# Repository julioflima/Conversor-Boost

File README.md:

# CONVERSOR BOOST

##### UNIVERSIDADE FEDERAL DO CEARÁ, CAMPUS SOBRAL
##### 
##### ENGENHARIA ELÉTRICA, DISCIPLINA ELETRÔNICA DE POTÊNCIA
##### 

##### 1. FLÁVIA PEROZA RUIZ
##### 2. JULIO CESAR FERREIRA LIMA
##### 3. MATHEUS PIRES DE FARIAS
##### 4. YARA MACHADO OLIVEIRA

> ISSO É APENAS UM RESUMO, PARA MAIOR RIQUEZA DE DETALHES VER A VERSÃO EM PDF "Relatório de Potência.pdf".

## 1. INTRODUÇÃO

Quando se trata de mudanças em níveis de tensão em corrente contínua, não é
possível ser feito através de transformadores. A conversão de uma tensão contínua de um
nível a outro e feita a partir de conversores CC.
Existem algumas topologias de circuitos conversores, dentre elas quatro se
destacam: buck, boost, buck-boost e cùk. Todas essas topologias são baseadas no uso de
chaves eletrônicas (diodos, MOSFETs, etc) e indutores. O uso de capacitores em circuitos
conversores é comum pois são usados como filtros da tensão de saída.
Esses conversores normalmente são usados como reguladores chaveados. A
regulação é feita a partir de um PWM de frequência e uma chave (MOSFET, TGJ ou
IGBT). Para um melhor entendimento do processo de chaveamento é necessário o
conceito inicial de tempo de chave aberta e fechada, em um período T e uma razão cíclica
(duty cycle). O princípio do duty cycle é mostrado na figura 1.
Figura 1: Chaveamento em uma tensão de entrada Vs.

### 1 .1. CONVERSOR BOOST

O conversor boost é um conversor chaveado elevador, ou seja, fornece um ganho
de tensão na saída. Além disso, também apresenta características de fonte de corrente na
entrada e fonte de tensão na saída. O circuito do conversor boost é mostrado na figura 2.

Analisando esse circuito em seus dois modos de operação referentes ao
chaveamento, chave aberta e chave fechada, podemos observar duas situações para a
variação de corrente do indutor.
Para as análises feitas a seguir, consideraremos as seguintes características do duty
cycle, como mostrada na figura 3 e a equação 1.1.

#### 1.1.1. Chave fechada

Analisando a figura 4, conversor com a chave fechada, percebemos que a tensão em
cima do indutor, VL, é a mesma que VS de entrada.

Considerando a taxa de variação da corrente como constante, aumentando
linearmente enquanto a chave estiver fechada, e que o tempo em que a chave permanece
fechada é DT,a variação da corrente pode ser calculada por:

#### 1.1.2. CHAVE ABERTA

A figura 5 demonstra o funcionamento do circuito com a chave aberta. Analisando
percebemos que a tensão em cima do indutor se torna (VS - VO).

Fazendo a mesma análise para a variação da corrente feita para a chave fechada,
consideramos o tempo de chave aberto como (1-D)T. A equação 1.4 nos fornece a
variação da corrente no indutor para o circuito com a chave aberta.

#### 1.1.3. Ganho

Tomando as equações 1.3 e 1.4 como referência e igualando, obtemos a expressão
de ganho do conversor boost, mostrada na equação 1.5.

#### 1.1.4. Cálculo da corrente

Em conversores ideais podemos considerar a potência de entrada e de saída como
as mesmas. A partir disso encontramos uma reação para a corrente média do indutor, dada
pela equação.

Partindo disso são determinados os valores máximos e mínimos da corrente no
indutor. Observamos através da figura 6 o valor médio e as variações.

#### 1.1.5. Indutância mínima

Para uma condução contínua de corrente no indutor, a corrente deve ser maior que
zero. Igualamos então a equação 1.7 a zero para obtermos a indutância mínima no modo
contínuo.

Vale ressaltar que este valor é o de indutância mínima, não é o mesmo usado no
projeto. O indutor usado no conversor será calculado através das equações 1.3 e 1.4, de
acordo com os parâmetros que serão usados no projeto.

#### 1.1.6. Ondulação de tensão na saída

De acordo com a forma de onda da figura 7 encontramos a carga no capacitor
apenas calculando a área coberta de ranhuras.

Partindo da equação 1.10, observamos que a corrente do capacitor é proporcional
à derivada da tensão de saída. Considerando que corrente é a derivada da carga em função
do tempo, obtemos a equação 1.11.

Com isso, encontramos a expressão característica da variação da tensão de saída
de um conversor boost.

#### 1.1.7. Corrente no diodo

No conversor boost, o diodo se encontra em série com o indutor quando a chave
está aberta, a forma de onda será similar à da corrente no indutor quando o a chave estiver
aberta e zero quando a chave estiver fechada, como mostra a figura 8.

### 1.2. GERADOR DE PWM

O CI usado para realizar o chaveamento do projeto é o SG3525, através de um
PWM (modulação por largura de pulso). O circuito montado é similar ao da figura 9, onde
em RX é feito o ajuste da razão cíclica e em R 1 a frequência.

Fonte: Práticas de laboratório de Eletrônica de Potência.
Teoricamente, a saída do SG3525 deveria ser ligada na chave (MOSFET). Porém,
ao realizar essa ligação direta poderia gerar riscos de queimar os componentes. No
projeto, foi montado um circuito de chaveamento do MOSFET.

#### 1.2.1. Circuito de chaveamento do mosfet

O circuito de chaveamento do MOSFET foi montado como na figura 10. A análise
do circuito apresentado na figura 10 é fundamentada em estados bem definidos de corte
e saturação do MOSFET, cujo sinal é gerado pelo drive de acionamento da figura 9.

Para um sinal de nível alto (5V), gerado por Vpulse, o transistor Q 2 entra em
saturação, conduzindo uma corrente no coletor de IC2. O divisor de tensão composto por
R 4 e R 5 garante que o transistor Q 3 entre em saturação e conduza uma corrente IE3, parte
dessa corrente é responsável pela condução do primeiro diodo (D 1 ). Com isso, Q 1 entra
em corte, fazendo com que um impulso elevado de corrente seja necessário e uma tensão
VGS surge entre gate (G) e source (S). Quando Vpulse gerar um sinal baixo (0V), o
transistor Q 2 entra em corte e não circulará a corrente IC2. Com isso, os terminais de base
e emissor do transistor Q 3 passam a ficar no mesmo potencial (15V), logo estará em
estado de corte. A carga armazenada no capacitor intrínseco do MOSFET, Cgs, contribui
para o aparecimento de uma tensão que polariza Q 1. O transistor Q 1 é levado a saturação
e drena rapidamente a carga armazenada da etapa anterior.

### 1.3. CARGA

Como carga foram usados 7 resistores de 39Ω e 10W em paralelo, resultando em
uma resistência equivalente de 18,18Ω e dissipando 70W de potência.

## 2. OBJETIVOS

Projetar um conversor boost com uma elevação de tensão de 15V na entrada para
35V na saída, com 70W de potência na saída. As ondulações máximas na corrente do
indutor, na tensão e na corrente de saída devem ser de 10%. Após isso, realizar a
comparação entre o que foi simulado e os resultados obtidos experimentalmente.

## 3. METODOLOGIA

Ao longo do projeto, sabia-se que muitas modificações seriam feitas e haveriam
muitas contas a se fazer e a se refazer. Devido a essa problemática, buscando otimizar o
tempo na determinação de parâmetros foi elaborada uma planilha, em que todas as
fórmulas foram inseridas de modo visual, assim como todas os cálculos. Cada variável
foi adotada um nome de forma que em caso de erro era possível visualizar a fórmula com
nomes e não mais apenas com um rótulo aleatório o que poderia ter gerado muitos erros.
No intuito de validar a planilha, todos os cálculos e resultados providos por ela
foram refeitos a mão, no entanto apenas uma vez, todas as outras vezes os cálculos foram
validados por esta prévia validação. No entanto com o uso a modificação de dados poderia
levar a modificação de fórmulas de maneira descontrolada e imprevisível sem a garantia
que alguém percebesse tal modificação. Com o objetivo de contornar esta problemática,
fora bloqueada todas as células da planilha que não fossem entrada de dados e apenas
permitidas as que correspondessem aos parâmetros de projeto, as variáveis de entrada se
encontram abaixo, juntamente com seus valores utilizados. Não fora adotada nenhuma
senha em caso de necessidade de mudança de algo, bastando apenas clicar no botão para
desbloquear, contudo o fato de obrigatoriamente ter de se clicar em um específico botão,
já garante um maior nível de confiabilidade nos cálculos. A planilha desenvolvida
encontra-se no repositório público [3].

No desenvolvimento das placas de circuito impresso, foi utilizado o software
Kicad, que é Open Source e agrega muito de outros softwares industriais como o Altium.
Com facilidade é possível gerar um projeto de eletrônica com este, uma vez que ele se
assemelha em muito a softwares de simulação como PSIM, Proteus, etc, no entanto ele
destina-se apenas ao design.
A maior facilidade que o Kicad oferece, é por conter uma vasta quantidade de
componentes de comuns no mercado, assim como o encapsulamento destes, muitos em
3 D. Outra grande vantagem na sua utilização, é na facilidade de se anexar novos
dispositivos encontrados por meio da Internet, por conta de uma vasta comunidade que

se dedica a compartilhar estes, assim como a concepção de novos componentes, inclusive
em 3D. A possibilidade de visualização em 3D possibilita que problemas de espaço
característicos desses tipos de projeto sejam resolvidos ainda durante a fase de projeto,
não onerando tempo na prototipagem [ANEXO 9.1]. Com isso o esquemático
desenvolvido em todos os circuitos está demonstrado no anexo [ANEXO 9. 2 ]. Também
fora disponibilizado uma visão da placa de circuito impresso com a legenda dos
componentes no intuito de facilitar a montagem [ANEXO 9.3]. Assim como foi
disponibilizado o arquivo, que se impresso e utilizada a técnica de produção de placas de
circuito impresso termotransferência, poderá ser reproduzido o protótipo aqui
desenvolvido [ANEXO 9.3].
Os arquivos aqui desenvolvidos, como esquemático e placa referentes ao software
Kicad, assim como as simulações desenvolvidas no software PSIM encontram-se no
repositório público [ 3 ].

## 4. PROCEDIMENTO

Para a implementação do conversor boost foram necessários cálculos para o
dimensionamento correto dos componentes. Para esses cálculos foram usados os
parâmetros da tabela 1.

### 4.1. CÁLCULOS DO CONVERSOR BOOST

#### 4.1.1. Resistência e tensão de saída

Para a escolha da tensão de saída, usamos como parâmetros os valores das
resistências de 10W que tínhamos disponíveis. Para obtenção do valor de potência
exigido (70W) utilizamos 7 resistores de 39Ω que dissipam 10W de potência, obtendo
uma carga equivalente de cerca de 18,18Ω. Com os resistores já definidos, partimos da
equação da potência para a definição da tensão de saída, que é demonstrada na equação
3.1.

Substituindo os valores fornecidos anteriormente, obtemos uma tensão de saída
de aproximadamente 35,67V

#### 4.1.2. Corrente média no indutor

Tomando como base a equação de ganho de um conversor boost e considerando
que a tensão da fonte adotada foi de 15V, podemos encontrar um valor para o duty cycle,
como mostrado na equação 3.2.

Adotando os valores mostrados acima obtemos um duty cycle de
aproximadamente 0,57952.
A corrente média no indutor pode ser calculada a partir da equação 3.3, já
demonstrada na introdução.

Obtendo assim uma corrente média no indutor de 4,6667A.

#### 4.1.3 Indutância mínima

Uma preocupação necessária no projeto do conversor é que o indutor opere de
modo contínuo, sendo assim, é necessário que asseguremos que o valor utilizado seja
superior ao valor obtido na expressão abaixo.

Assim, para garantir que o indutor opere de modo contínuo, garantindo que a
corrente que passe por ele seja sempre positiva, se faz necessário assegura-se que o valor
do indutor utilizado seja maior que o calor obtido a partir da equação 3.4.

#### 4.1.4 Cálculo do indutor

Primeiramente foi calculado a corrente de entrada de acordo com a
potência de saída e a tensão de entrada.

#### 4.1.4.1 Corrente no indutor

A partir da equação que segue, podemos obter a corrente de entrada, que é igual a
corrente no indutor.

#### 4.1.4.2 Corrente de saída

Utilizando a potência de saída e a tensão de saída, podemos obter a corrente de
saída a partir da equação abaixo:

Com os valore obtidos, finalmente podemos calcular o valor teórico do indutor,
de acordo com a tensão de saída, ondulação de corrente de entrada, o ciclo de trabalho e
a frequência a partir da equação que segue, levando em consideração que a ondulação de
corrente deve estar em função da tensão de entrada, do ciclo de trabalho, a indutância e a
frequência, ∆i:

O indutor implementado na prática foi feito de forma manual, obtendo um valor
de 1,5 mH, garantindo dessa forma a ondulação de corrente no mesmo em um valor de
10%.

#### 4.1.5 Cálculo do capacitor

Tendo como sendo 10% de ondulação de saída uma das limitações do projeto,
temos que tomar esse parâmetro para projetar o capacitor capaz de atender a essa
demanda. Para tal, foi utilizado a equação que segue:

Na prática utilizamos um capacitor 22uF, que foi o suficiente para que o
ripple da tensão sobre o capacitor não ultrapassasse os 10%.

### 4.2. DIMENSIONAMENTO DO INDUTOR

#### 4.2.1. Núcleos magnéticos

Para a construção o mais próximo do ideal do conversor, todos os elementos que
o constituem devem ser devidamente projetados, porém na construção de conversores
CC-CC, fatores como o surgimento de componentes parasitas devem ser levados em
consideração, como por exemplo: Capacitâncias parasitas, indutâncias de magnetização,
etc.
Na construção do núcleo magnético do indutor geralmente é usado um material
chamado ferrite, composto por óxido de ferro e possui poucas perdas quando é utilizado

em altas frequências, tendo como um dos problemas da sua utilização a sua fragilidade,
podendo ser comparada a fragilidade do vidro comum.

Duas informações importantes do núcleo são a Área de secção transversal (Ae) e
a Área da Janela (Aw). Dados esses dois valores, pode-se calcular os demais dados do
mesmo.
Figura 12: Núcleo de Ferrite tipo E-E, enfatizando suas áreas de janela e
transversal.

#### 4.2.2. Cálculos dos parâmetros.

O projeto do indutor se baseia nas Leis de Faraday e Àmpere, onde através de
algumas manipulações matemáticas se obterá:

#### 4.2.4. Entreferro

É necessário a utilização do entreferro no circuito magnético, sendo a indutância
proporcional ao número de espiras ao quadrado e inversamente proporcional a relutância.
Por mais alta que seja a permeabilidade magnética do material, ele possui uma
relutância. Nesse caso o valor da indutância independe da relutância do núcleo, assim:

O valor do entreferro será distribuído igualmente nas pernas
laterais do núcleo.

#### 4.2.5. Secção dos condutores

Considerando que o conversor opera em uma alta frequência, devido ao seu
chaveamento, assim, um efeito pelicular considerável, uma vez que a densidade de
corrente ficará na periferia, causando uma redução na área efetiva do condutor.
A equação a seguir define qual a bitola do condutor para conduzir a corrente do
enrolamento:

Assim sendo necessário calcular o número de condutores em paralelo para que
seja possível a condução da corrente necessária sem que exista um superaquecimento
dos mesmos.

Para a última etapa do projeto do indutor, temos que verificar se é possível
associar estes condutores na janela do núcleo. Assim, se Ex<1 é possível a utilização
deste núcleo, verificando essa máxima, utilizamos:

### 4.3. CIRCUITO SIMULADO

Após os cálculos dos parâmetros do conversor Boost, o mesmo foi simulado
utilizando o software PSIM para que posteriormente pudesse ser implementado no
circuito físico.

A tensão na fonte, onda em azul, é constante, visto que este é um conversor
CC-CC e foi implementada uma fonte de tensão contínua de 15V. Já a corrente
passa apenas pelo indutor com a chave fechada, carregando-o e, quando a chave
está aberta, ele é descarregado através do capacitor e carga, passando pelo diodo,
com corrente eficaz de 4,66A.

Na figura 13 observa-se as formas de onda de tensão (em azul) e de
corrente (vermelha) na carga a partir do momento que o conversor é ligado. A
ondulação de tensão de saída corresponde a 6 ,85% da tensão rms, que é de 35,68V
e a ondulação de corrente na carga também é de 6 ,85% da corrente rms, que é
1 , 96 퐴. Para melhor observar estas formas de onda na carga, elas são apresentadas
ampliadas na figura 14.

Com isso, é mostrada também a potência ativa de saída, igual a 69,94W,
praticamente igual à potência solicitada nas especificações, que é de 70W.

Para melhor visualização da forma de onda a mesma foi ampliada, obtendo
o mostrado na figura 16.

Com a chave fechada a corrente que sai da fonte passa totalmente pelo
indutor, que se carrega e se mantém assim até que a chave abra e ele comece a
descarregar pelo capacitor, por isso a onda é desta forma, com valor rms igual a
18,14V.

O mesmo ocorre para a forma de onda da corrente, foi mostrado desde o
momento em que o circuito começa seu funcionamento na figura 17, mas para
melhor analisá-la é necessário dar zoom.

O valor rms da corrente no indutor é de 4,66A e ela aumenta enquanto a
chave está fechada e começa a decair quando a chave se abre. A ondulação de
corrente nesse componente é de 5 ,94%, um valor dentro do aceitável.

O valor eficaz de tensão na chave obtido nesta simulação é de 25,30V e o
de corrente é de 3,30A. Como no software os componentes são tratados como
ideal, quando não há corrente na chave a tensão na mesma é máxima, visto que
ela está aberta, podendo ser considerada um circuito aberto. Já quando a tensão é
nula, a corrente é máxima, então a chave pode ser considerada um curto-circuito.
Figura 21: Formas de Onda de Tensão e Corrente no Diodo

O valor eficaz de tensão no diodo é de 24,28V  e de corrente é equivalente
a 3,40A. A partir das formas de onda acima é possível notar que quando há
corrente no diodo a tensão no mesmo é nula, pois, como é considerado ideal, se
comporta como um curto-circuito, do mesmo modo que ocorre com a chave
mostrada anteriormente. Já quando o diodo está em aberto a tensão é negativa pois
é a tensão reversa nele, que possui valor igual à tensão na carga (aproximadamente
36V), porém com sinal oposto.

## 5. EXPERIMENTO

### 5.1. CIRCUITO DE CHAVEAMENTO

O circuito de drive montado é o demonstrado na figura 22, um integrador que gera
uma onda PWM em dois canais. Foram feitos os ajustes necessários para suprir as
especificações do projeto, a uma frequência de 20kHz a fim de obter o chaveamento
necessário para o Mosfet(IRF640), a partir disso dimensionamos o valor do capacitor C 1
para 10nF, R 1 é um resistor variável (Trimpot 50K), onde podemos realizar o ajuste para
obter a frequência ideal. Para o resistor Ry foi usado um resistor de 10K. Em Rx também
foi usado um resistor variável (Trimpot 50K), para ser feito o ajuste do duty-cycle.

Um circuito totem pole foi usado para melhoria do funcionamento do driver. Esse
circuito é obtido através da associação de dois diodos para aumentar o duty-cycle a partir
das tuas portas do CI-3525, obtendo uma onda de até cerca de 90% de ciclo de trabalho.
Os diodos usados foram do tipo Shotcky, de modo que o tempo de recuperação fosse
baixo.

Usando o osciloscópio para medir a onda do chaveamento PWM, obtemos as
formas especificadas na figura 23. Vale destacar que o driver foi alimentado com uma
tensão de 15V e frequência de 20kHz.
Figura 23 : Forma de onda do PWM (laranja) x Tensão na saída (azul)

### 5.2. CIRCUITO DE POTÊNCIA

Após os cálculos e simulações feitas no PSIM, foi realizada a montagem da parte
prática, como mostrado na figura 24 e 25.

Após a montagem do circuito foram feitas as devidas medições. Os parâmetros
estabelecidos pela equipe eram de 15V na entrada e 35V na saída.

Fonte: Autores
Ao compararmos a onda obtida com a simulada, observamos que a onda medida
contém leves ruídos, porém estes não são de grande relevância na medição da tensão final,
gerando uma tensão de 14,8V, o que representa uma diferença de cerca de 1,33% do valor
previamente estabelecido. Com a placa alimentada nos 15V de entrada, a tensão na saída
foi medida. O valor médio encontrado foi de 35,9V, possuindo um erro de cerca de 1,02%
do valor estipulado, observados na figura 26. Comparando com a simulação, o resultado
foi bem satisfatório.

Com a alicate amperímetro do osciloscópio, foram medidos os valores de corrente
na carga, que estão comparados aos de tensão.

O valor de corrente médio obtido gira em torno de 2%. Sendo assim, notamos que
o conversor boost projetado está gerando resultados satisfatórios e coerentes com a
simulação.

### 5.3. CIRCUITO DE CARGA

Com o intuito de verificar de fato a potência calculada fora montada uma placa
exclusivamente para teste, que consistem em uma associação de resistores (3x 150Ω, 3x
120Ω e 1x 100Ω) todos em paralelo que combinadas dão aproximadamente a resistência
de carga 18.18Ω, na prática devido a tolerância dos resistores a resistência de carga
modificou-se um pouco ao que foi estimado, no entanto o circuito ainda comportou-se de
forma estável superando os cálculos de potência. Segue abaixo a figura 27 do resultado.

As chaves encontradas na placa possibilitam o teste com variação de carga, assim
como também um distúrbio, em caso de futura implementação de uma malha fechada por
meio de um controle. A placa de driver, já está pronta para essa expansão, contando com
bornes de saída para alimentação do controlador, assim como um borne de entrada com
o valor da saída do controlador. Nesse intuito poderiam ser utilizados controladores PID
e PI, pelo menos. Desse modo os efeitos provocados pela variação da carga, seriam
estabilizados por meio dos controladores, assim a tensão deveria ainda ficar estável, sem
necessidade de modificação do duty-cicle de modo manual, a modificação deste ficaria a
cargo do controlador.

## 6. CONCLUSÃO

Em resumo, o conversor Boost funciona sendo alimentado por uma tensão CC e a
eleva na saída de forma que essa tensão também seja constante. Como os dispositivos
utilizados são chave, diodo, indutor, capacitor e resistor e a maioria deles opera como
circuito aberto ou como curto circuito em diferentes momentos, há uma certa ondulação
de tensão e corrente na carga, porém dentro do aceitável de acordo com as especificações
de projeto.
A simulação do circuito foi de suma importância para analisar seu funcionamento
e comportamento quando alguns parâmetros eram modificados, assim alterações
poderiam ser feitas antes da execução do projeto na placa. Apesar de ser possível fazer
determinadas previsões, deve-se lembrar que a teoria e a prática diferem um pouco, visto
que em cálculos e em simulações são considerados componentes ideais, e não reais. Os
elementos reais dissipam calor, perdendo energia, entre outros fatores como a obtenção
manual do indutor calculado, que fazem com que a execução do projeto se torne mais
difícil.
É relevante citar foi necessário implementar dissipadores, pois componentes como
o MOSFET dissipam muito calor, dada a potência trabalhada, que é de 70W. Além disso,
para que o conversor funcionasse com um duty cycle maior que 0,5 foi preciso utilizar as
duas saídas do CI SG3525 num pequeno circuito eletrônico que somasse as duas, pois o
ciclo de trabalho do projeto em questão era de 0,58.
Pelo fato de não ser controlado, caso este conversor CC-CC do tipo Boost tenha
alguns de seus parâmetros alterados, os demais não serão ajustados, obtendo valores
diferentes dos esperados.
Com isso, na execução do projeto final da disciplina de Eletrônica de Potência,
observou-se a importância de um bom planejamento e estudo do funcionamento do
circuito a ser implementado. Em função disso, o conversor teve uma boa resposta e, como
esperado, elevou a tensão de 15V de entrada para uma tensão de 35V de saída, ambas
contínuas, com a carga estabelecida, obedecendo os parâmetros de projeto, possibilitando
um maior conhecimento prático desse conteúdo, além das práticas em laboratório.

## 7. REFERÊNCIAS BIBLIOGRÁFICAS

```
[1] Hart, D. W. (2012). Eletrônica de Potência. (R. Abdo, Trad.) Porto Alegre,
Rio Grande do Sul, Brasil: AMGH Editora Ltda.
[2] BARBI, Ivo. (2011). Projetos de fontes chaveadas. Florianópolis: Edição do
Autor.
```

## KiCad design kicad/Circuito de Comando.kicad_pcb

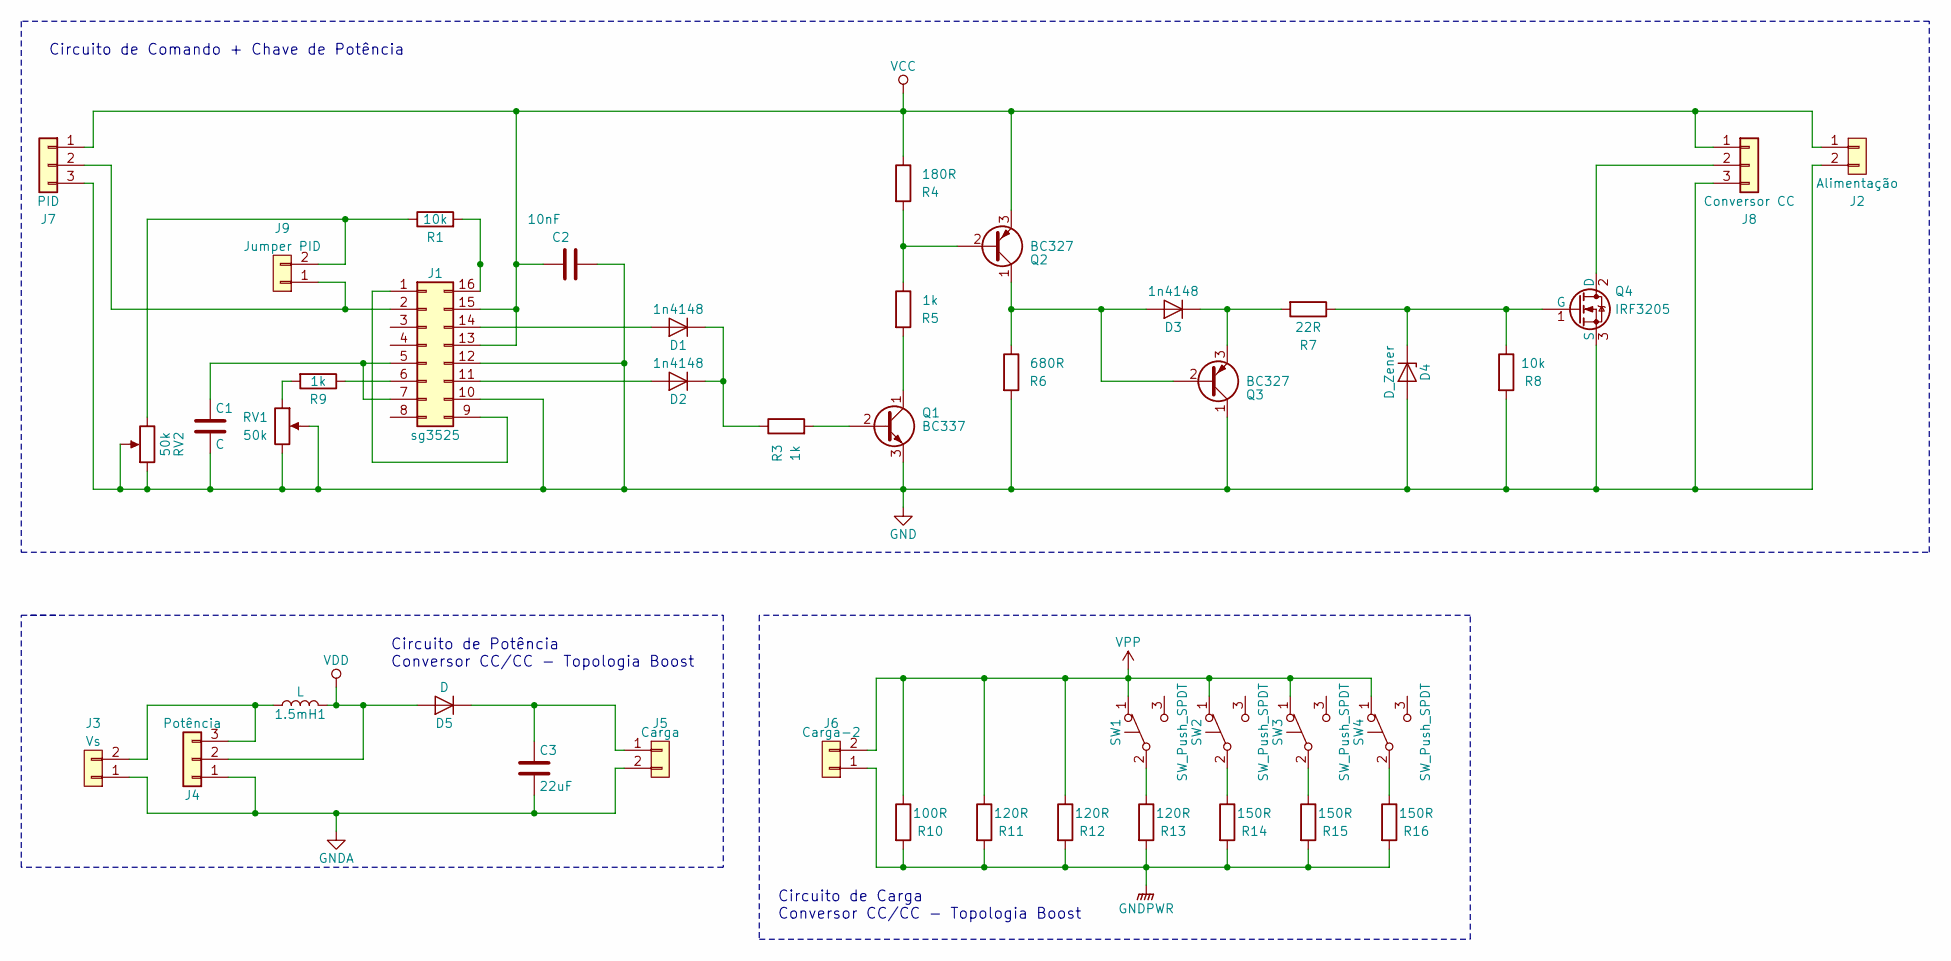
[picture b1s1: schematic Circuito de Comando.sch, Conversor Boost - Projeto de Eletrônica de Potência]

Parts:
1.5mH1: L; L_Toroid_Vertical_L67.6mm_W36.1mm_P31.80mm_Vishay_TJ9
C1: C; CP_Radial_D8.0mm_P5.00mm
C2: 10nF; CP_Radial_D8.0mm_P5.00mm
C3: 22uF; CP_Radial_D8.0mm_P5.00mm
D1, D2, D3: 1n4148; D_DO-35_SOD27_P7.62mm_Horizontal
D4: D_Zener; D_DO-35_SOD27_P7.62mm_Horizontal
D5: D; TO-220-2_Vertical
J1: sg3525; DIP-16_W7.62mm_LongPads
J2: Alimentação; TerminalBlock_Phoenix_MKDS1.5-2pol
J3: Vs; TerminalBlock_Phoenix_MKDS1.5-2pol
J4: Potência; TerminalBlock_Phoenix_MKDS1.5-3pol
J5: Carga; TerminalBlock_Phoenix_MKDS1.5-2pol
J6: Carga-2; TerminalBlock_Phoenix_MKDS1.5-2pol
J7: PID; TerminalBlock_Phoenix_MKDS1.5-3pol
J8: Conversor CC; TerminalBlock_Phoenix_MKDS1.5-3pol
J9: Jumper PID; Pin_Header_Straight_1x02_Pitch2.54mm
Q1: BC337; TO-92_Molded_Narrow
Q2, Q3: BC327; TO-92_Molded_Narrow
Q4: IRF3205; TerminalBlock_Phoenix_MKDS1.5-3pol
R1: 10k; Potentiometer_WirePads
R3, R5, R9: 1k; R_Axial_DIN0204_L3.6mm_D1.6mm_P7.62mm_Horizontal
R4: 180R; R_Axial_DIN0204_L3.6mm_D1.6mm_P7.62mm_Horizontal
R6: 680R; R_Axial_DIN0204_L3.6mm_D1.6mm_P7.62mm_Horizontal
R7: 22R; R_Axial_DIN0204_L3.6mm_D1.6mm_P7.62mm_Horizontal
R8: 10k; R_Axial_DIN0204_L3.6mm_D1.6mm_P7.62mm_Horizontal
R10: 100R; R_Axial_Power_L48.0mm_W12.5mm_P55.88mm
R11, R12, R13: 120R; R_Axial_Power_L48.0mm_W12.5mm_P55.88mm
R14, R15, R16: 150R; R_Axial_Power_L48.0mm_W12.5mm_P55.88mm
RV1, RV2: 50k; Potentiometer_Trimmer_ACP_CA6v_Horizontal
SW1, SW2, SW3, SW4: SW_Push_SPDT; power_switch

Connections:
GND: C1.2, C2.2, D4.2 (A), J1.10, J1.12, J2.2, J7.3, J8.3, Q1.3 (E), Q3.1 (C), Q4.3 (S), R6.2, R8.2, RV1.2, RV1.3, RV2.1, RV2.2
GNDA: C3.2, J3.1, J4.1, J5.2
GNDPWR: J6.1, R10.2, R11.2, R12.2, R13.2, R14.2, R15.2, R16.2
unnamed: 1.5mH1.1, J3.2, J4.3
unnamed: C1.1, J1.5, J1.7
unnamed: C3.1, D5.1 (K), J5.1
unnamed: D1.1 (K), D2.1 (K), R3.1
unnamed: D1.2 (A), J1.14
unnamed: D2.2 (A), J1.11
unnamed: D3.1 (K), Q3.3 (E), R7.2
unnamed: D3.2 (A), Q2.1 (C), Q3.2 (B), R6.1
unnamed: D4.1 (K), Q4.1 (G), R7.1, R8.1
unnamed: J1.1, J1.9
unnamed: J1.2, J7.2, J9.1
unnamed: J1.6, R9.1
unnamed: J1.16, R1.2
unnamed: J8.2, Q4.2 (D)
unnamed: J9.2, R1.1, RV2.3
unnamed: Q1.1 (C), R5.2
unnamed: Q1.2 (B), R3.2
unnamed: Q2.2 (B), R4.2, R5.1
unnamed: R9.2, RV1.1
unnamed: R13.1, SW1.2 (B)
unnamed: R14.1, SW2.2 (B)
unnamed: R15.1, SW3.2 (B)
unnamed: R16.1, SW4.2 (B)
VCC: C2.1, J1.13, J1.15, J2.1, J7.1, J8.1, Q2.3 (E), R4.1
VDD: 1.5mH1.2, D5.2 (A), J4.2
VPP: J6.2, R10.1, R11.1, R12.1, SW1.1 (A), SW2.1 (A), SW3.1 (A), SW4.1 (A)

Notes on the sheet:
Circuito de Potência Conversor CC/CC - Topologia Boost
Circuito de Comando + Chave de Potência
Circuito de Carga Conversor CC/CC - Topologia Boost

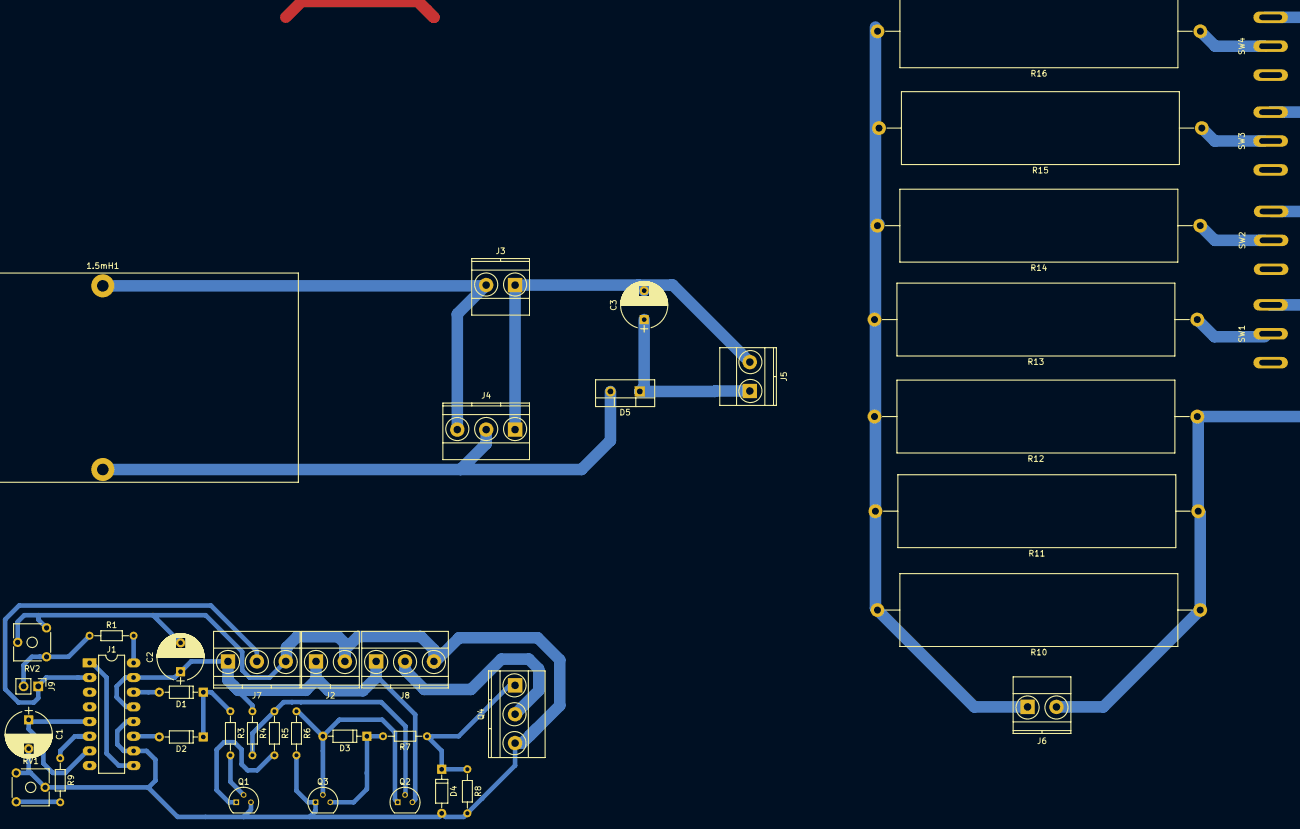
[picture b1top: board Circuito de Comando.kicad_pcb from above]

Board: 2 copper layers, 43 parts (0 on the bottom side), 29 nets.

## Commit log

2018-06-19 add project
2018-06-19 remove old files
2018-06-19 add schematics
2018-06-19 add report
2018-06-19 add readme
2018-06-19 edit 1
2018-06-19 edit 2
2018-06-19 edit 3.
2018-06-19 edit3
2018-06-19 edit4
2018-06-19 edit5
